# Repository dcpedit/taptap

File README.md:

# TapTap

TapTap is a solenoid breakout board for those who are interested in adding a solenoid to their existing project.  All you need are the following components, and an extra data pin on your microcontroller.

| Component              | Qty | Notes |
| ---------              | --- | ----- |
| TIP120 transistor      | 1   | [Link](https://www.mouser.com/ProductDetail/STMicroelectronics/TIP120?qs=ljbEvF4DwOPl3O93r6IAPg%3D%3D&countryCode=US&currencyCode=USD)
| 1N4001 diode           | 1   | [Link](https://www.mouser.com/ProductDetail/Comchip-Technology/1N4001T-G?qs=tw%252BuQ%2FB6PO0RYol0pdT1tQ%3D%3D&countryCode=US&currencyCode=USD)
| 2.2K resistor          | 1   | [Link](https://www.mouser.com/ProductDetail/Vishay-BC-Components/MBA02040C2201FRP00?qs=xrHRiZ6CCZBgw9ermhhPGg%3D%3D&countryCode=US&currencyCode=USD)
| 5V solenoid            | 1   | [Link](https://www.mouser.com/ProductDetail/SparkFun/ROB-11015?qs=WyAARYrbSnb40pNKVm6nzg%3D%3D&mgh=1&gclid=CjwKCAjw7eSZBhB8EiwA60kCWzuptoTvtKnuIf080uSxeGzK6HKDzFasQVXGcZVyhToXtIho5E1QCRoCD08QAvD_BwE)

Here's an example of how I used one in a [QAZer Beam](https://github.com/ImYourHuckleberry/QAZER_BEAM)

And another in my [Pillz Mod project](https://github.com/dcpedit/pillzmod)

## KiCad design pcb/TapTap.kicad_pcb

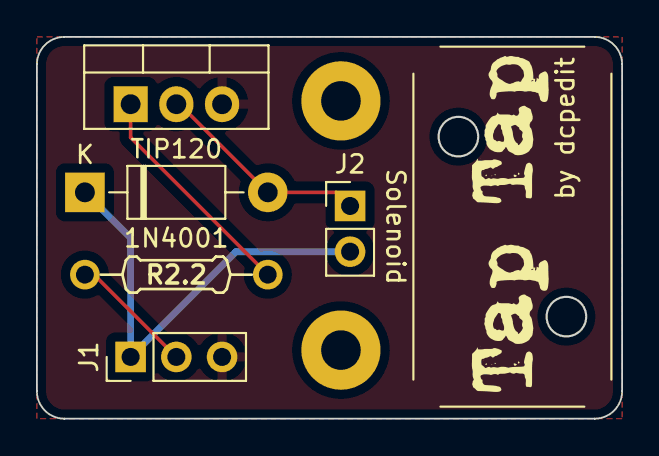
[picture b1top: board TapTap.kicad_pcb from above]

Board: 2 copper layers, 32.5 x 21.2 mm, 8 parts (0 on the bottom side), 5 nets.

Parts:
1N4001: 1N4001; D_DO-41_SOD81_P10.16mm_Horizontal
H1, H2: MountingHole; MountingHole_2.2mm_M2_Pad
J1: Conn_01x03_Female; PinHeader_1x03_P2.54mm_Vertical
J2: Conn_01x02_Female; PinHeader_1x02_P2.54mm_Vertical
R2.2: R_2.2; Resistor
Solenoid: solenoid
TIP120: TIP120; TO-220-3_Vertical

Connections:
+5V: 1N4001.1 (K), J1.1, J2.2
GND: J1.3, TIP120.3 (E)
unnamed: 1N4001.2 (A), J2.1, TIP120.2 (C)
unnamed: J1.2, R2.2.1
unnamed: R2.2.2, TIP120.1 (B)

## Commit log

2022-10-03 Add readme
2024-11-11 Add example in readme
